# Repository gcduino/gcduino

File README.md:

GCDuino 
=======
© 2013-2014 Steve Dalton & Rod Christian

GCDuindo is a small low cost Arduino platform created by [Rod Christian](http://github.com/Rod-Refactor) and [Steve Dalton](http://github.com/spidie) of [Gold Coast TechSpace](http://gctechspace.org)

How to checkout this code
-------------------------

    git clone git@github.com:gctechshop/gcduino.git

Project Guide & Documentation
-----------------------------

For a work in progress project guide that we are using for the [Gold Coast TechSpace Discovery Workshops](http://discovery.gctechspace.org), please visit our [wiki](http://github.com/gcduino/gcduino/wiki)

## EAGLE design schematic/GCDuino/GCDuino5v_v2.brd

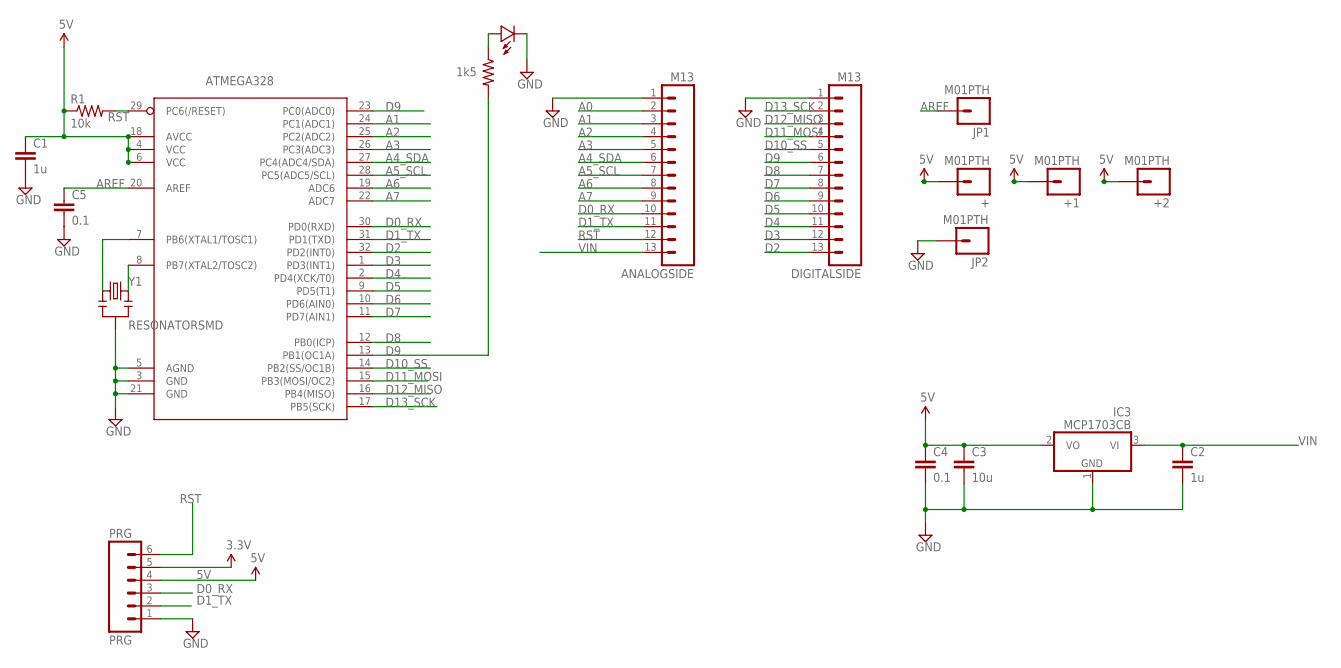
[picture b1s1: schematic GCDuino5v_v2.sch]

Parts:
+, +1, +2: M01PTH; 1X01
ANALOGSIDE: M13; 1X13
ATMEGA328: ATMega-328; TQFP32-08
C1, C2: 1u; 0805
C3: 10u; 0805-CAP
C4, C5: 0.1; 0805
DIGITALSIDE: M13; 1X13
IC3: MCP1703CB; SOT23
JP1, JP2: M01PTH; 1X01
PRG: PRG; 1X06
R1: 10k; 0805
R2: 1k5; 0805
U$2: LED0805; 0805-LED
Y1: RESONATORSMD; RESONATOR-SMD

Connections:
3.3V: PRG.5
5V: +.1, +1.1, +2.1, ATMEGA328.4 (VCC), ATMEGA328.6 (VCC), ATMEGA328.18 (AVCC), C1.1, C3.1, C4.1, IC3.2 (VO), PRG.4, R1.1
A0: ANALOGSIDE.2, ATMEGA328.23 (PC0(ADC0))
A1: ANALOGSIDE.3, ATMEGA328.24 (PC1(ADC1))
A2: ANALOGSIDE.4, ATMEGA328.25 (PC2(ADC2))
A3: ANALOGSIDE.5, ATMEGA328.26 (PC3(ADC3))
A4_SDA: ANALOGSIDE.6, ATMEGA328.27 (PC4(ADC4/SDA))
A5_SCL: ANALOGSIDE.7, ATMEGA328.28 (PC5(ADC5/SCL))
A6: ANALOGSIDE.8, ATMEGA328.19 (ADC6)
A7: ANALOGSIDE.9, ATMEGA328.22 (ADC7)
AREF: ATMEGA328.20 (AREF), C5.1, JP1.1
D0_RX: ANALOGSIDE.10, ATMEGA328.30 (PD0(RXD)), PRG.3
D1_TX: ANALOGSIDE.11, ATMEGA328.31 (PD1(TXD)), PRG.2
D2: ATMEGA328.32 (PD2(INT0)), DIGITALSIDE.13
D3: ATMEGA328.1 (PD3(INT1)), DIGITALSIDE.12
D4: ATMEGA328.2 (PD4(XCK/T0)), DIGITALSIDE.11
D5: ATMEGA328.9 (PD5(T1)), DIGITALSIDE.10
D6: ATMEGA328.10 (PD6(AIN0)), DIGITALSIDE.9
D7: ATMEGA328.11 (PD7(AIN1)), DIGITALSIDE.8
D8: ATMEGA328.12 (PB0(ICP)), DIGITALSIDE.7
D9: ATMEGA328.13 (PB1(OC1A)), DIGITALSIDE.6, R2.2
D10_SS: ATMEGA328.14 (PB2(SS/OC1B)), DIGITALSIDE.5
D11_MOSI: ATMEGA328.15 (PB3(MOSI/OC2)), DIGITALSIDE.4
D12_MISO: ATMEGA328.16 (PB4(MISO)), DIGITALSIDE.3
D13_SCK: ATMEGA328.17 (PB5(SCK)), DIGITALSIDE.2
GND: ANALOGSIDE.1, ATMEGA328.3 (GND), ATMEGA328.5 (AGND), ATMEGA328.21 (GND), C1.2, C2.2, C3.2, C4.2, C5.2, DIGITALSIDE.1, IC3.1 (GND), JP2.1, PRG.1, U$2.MINUS, Y1.2
unnamed: ATMEGA328.7 (PB6(XTAL1/TOSC1)), Y1.1
unnamed: R2.1, U$2.PLUS
unnamed: ATMEGA328.8 (PB7(XTAL2/TOSC2)), Y1.3
RST: ANALOGSIDE.12, ATMEGA328.29 (PC6(/RESET)), PRG.6, R1.2
VIN: ANALOGSIDE.13, C2.1, IC3.3 (VI)

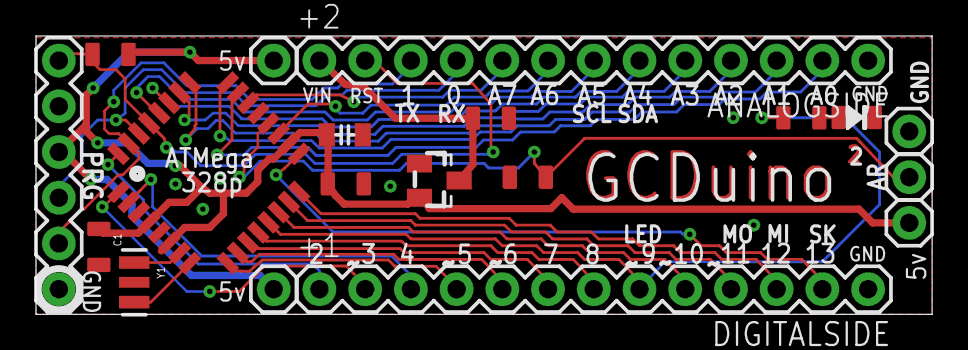
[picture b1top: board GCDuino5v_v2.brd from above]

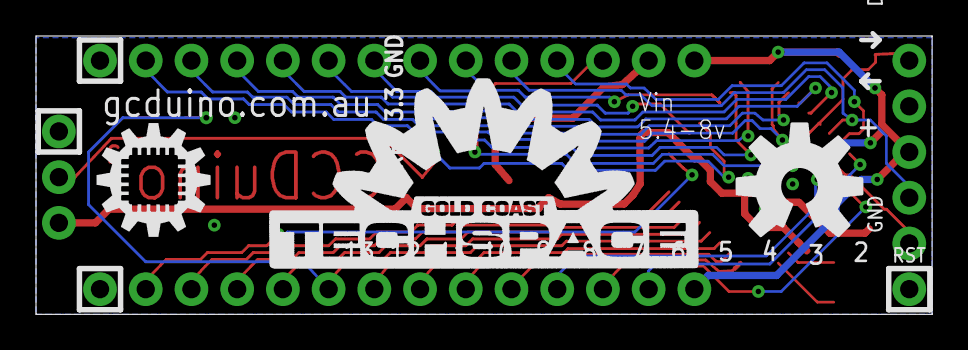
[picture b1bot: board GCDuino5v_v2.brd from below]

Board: 2 copper layers, 49.8 x 15.5 mm, 22 parts (3 on the bottom side), 30 nets.

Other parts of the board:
U$6: ID_LOGO_X0.25
U$7: OSHW-LOGO-L
U$9: GCTS_X0.5_TSILK

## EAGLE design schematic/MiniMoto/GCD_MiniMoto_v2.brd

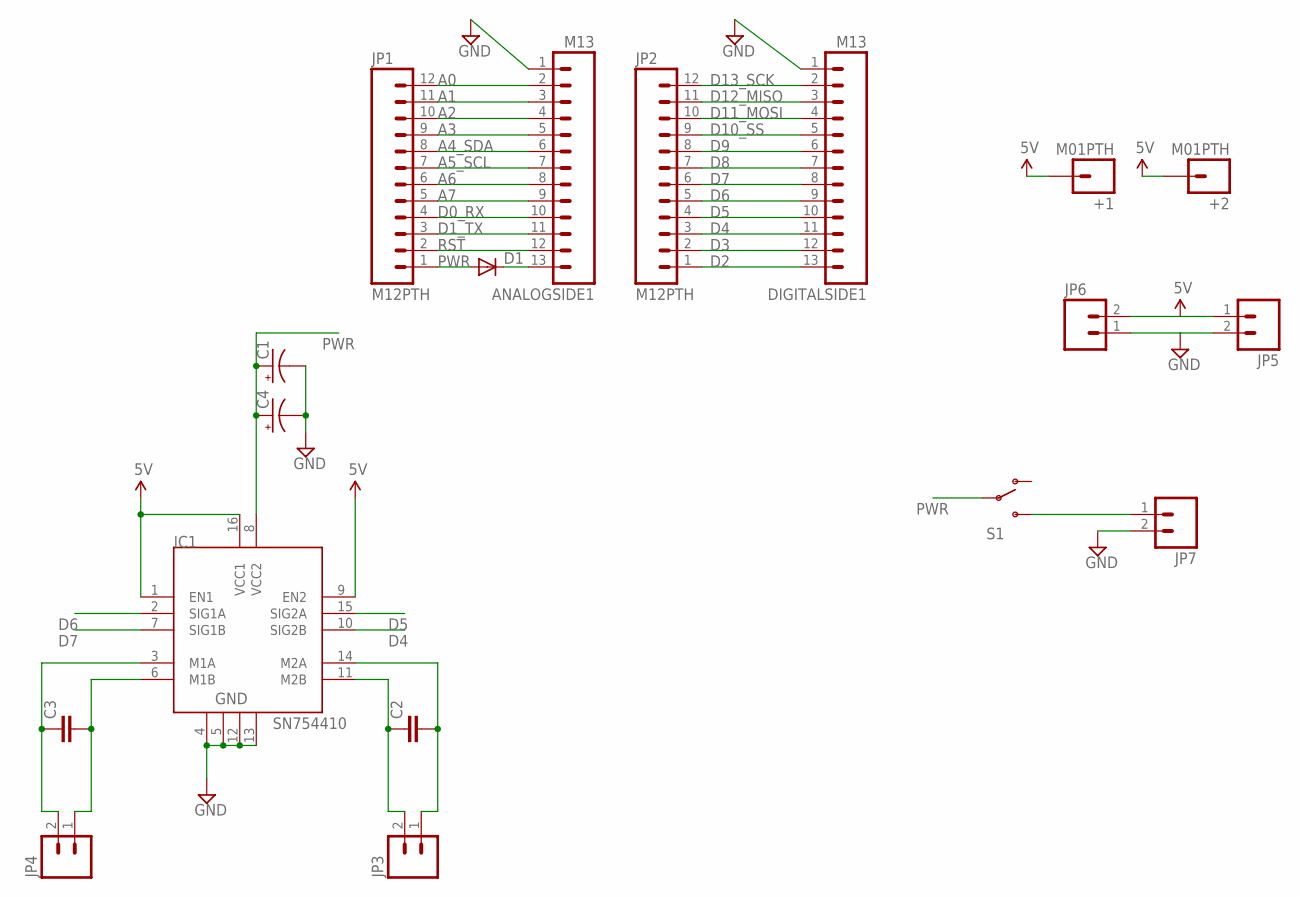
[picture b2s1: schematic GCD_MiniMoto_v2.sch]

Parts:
+1, +2: M01PTH; 1X01
ANALOGSIDE1: M13; 1X13
C1, C4: CAP_POLPTH1; CPOL-RADIAL-100UF-25V
C2, C3: CAPPTH1; CAP-PTH-5MM
D1: DIODESOD; SOD-323
DIGITALSIDE1: M13; 1X13
IC1: SN754410; DIP16
JP1, JP2: M12PTH; 1X12
JP3, JP4: M025MM; SCREWTERMINAL-5MM-2
JP5, JP6, JP7: M02PTH; 1X02
S1: SWITCH-SPDTPTH; SWITCH-SPDT

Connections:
5V: +1.1, +2.1, IC1.1 (EN1), IC1.9 (EN2), IC1.16 (VCC1), JP5.1, JP6.2
A0: ANALOGSIDE1.2, JP1.12
A1: ANALOGSIDE1.3, JP1.11
A2: ANALOGSIDE1.4, JP1.10
A3: ANALOGSIDE1.5, JP1.9
A4_SDA: ANALOGSIDE1.6, JP1.8
A5_SCL: ANALOGSIDE1.7, JP1.7
A6: ANALOGSIDE1.8, JP1.6
A7: ANALOGSIDE1.9, JP1.5
D0_RX: ANALOGSIDE1.10, JP1.4
D1_TX: ANALOGSIDE1.11, JP1.3
D2: DIGITALSIDE1.13, JP2.1
D3: DIGITALSIDE1.12, JP2.2
D4: DIGITALSIDE1.11, IC1.10 (SIG2B), JP2.3
D5: DIGITALSIDE1.10, IC1.15 (SIG2A), JP2.4
D6: DIGITALSIDE1.9, IC1.2 (SIG1A), JP2.5
D7: DIGITALSIDE1.8, IC1.7 (SIG1B), JP2.6
D8: DIGITALSIDE1.7, JP2.7
D9: DIGITALSIDE1.6, JP2.8
D10_SS: DIGITALSIDE1.5, JP2.9
D11_MOSI: DIGITALSIDE1.4, JP2.10
D12_MISO: DIGITALSIDE1.3, JP2.11
D13_SCK: DIGITALSIDE1.2, JP2.12
GND: ANALOGSIDE1.1, C1.2 (-), C4.2 (-), DIGITALSIDE1.1, IC1.4, IC1.5, IC1.12, IC1.13, JP5.2, JP6.1, JP7.2
unnamed: C3.1, IC1.3 (M1A), JP4.2
unnamed: C3.2, IC1.6 (M1B), JP4.1
unnamed: JP7.1, S1.3 (S)
unnamed: C2.1, IC1.11 (M2B), JP3.2
unnamed: C2.2, IC1.14 (M2A), JP3.1
unnamed: ANALOGSIDE1.13, D1.1 (C)
PWR: C1.1 (+), C4.1 (+), D1.2 (A), IC1.8 (VCC2), JP1.1, S1.2
RST: ANALOGSIDE1.12, JP1.2

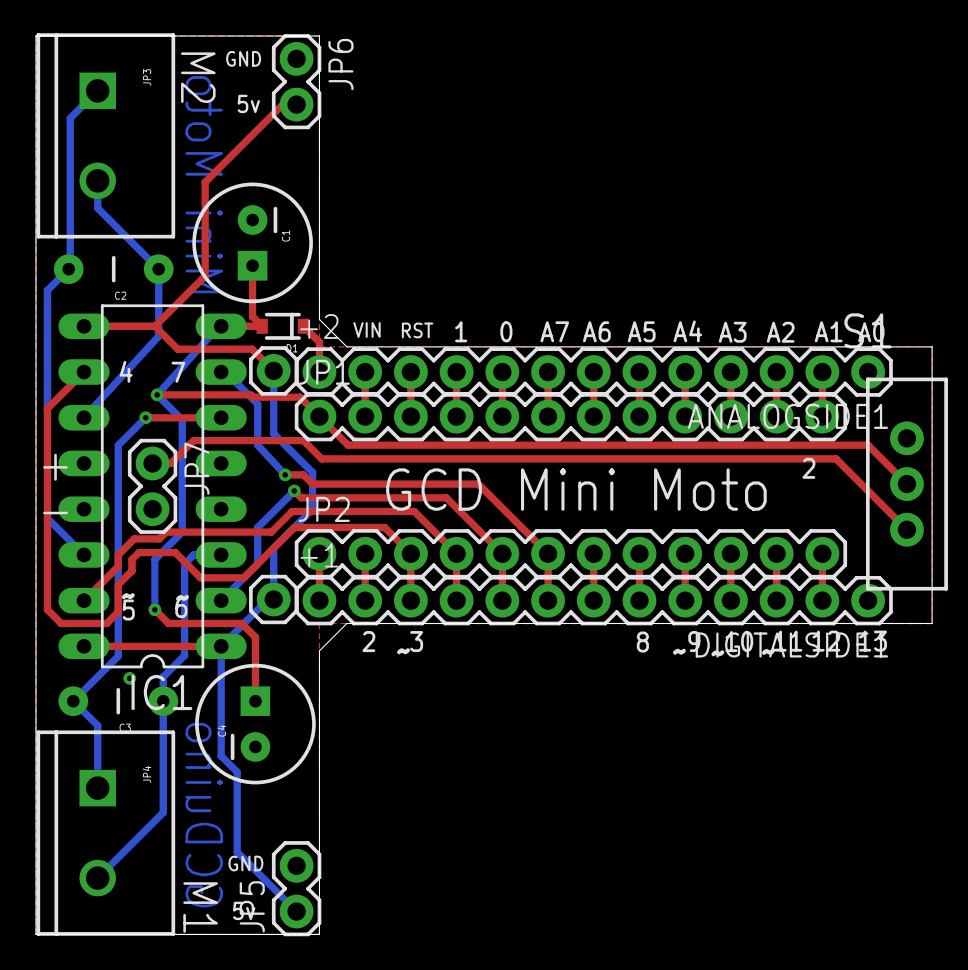
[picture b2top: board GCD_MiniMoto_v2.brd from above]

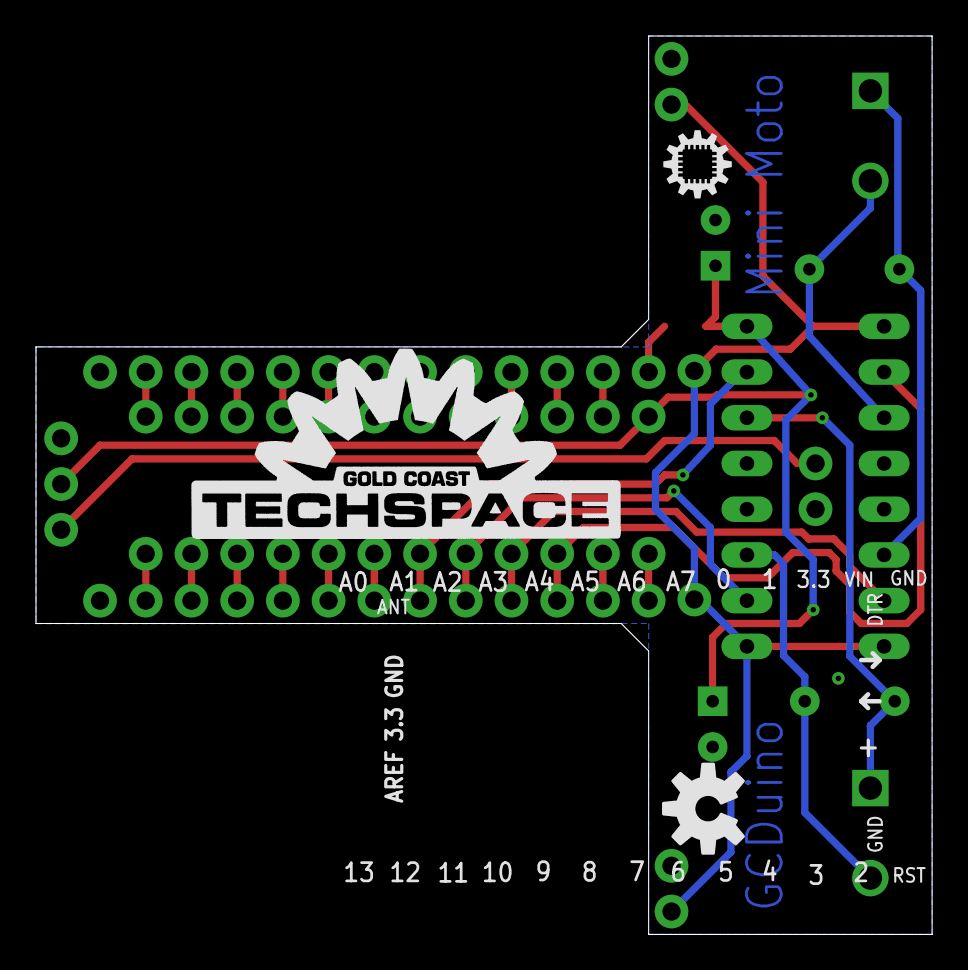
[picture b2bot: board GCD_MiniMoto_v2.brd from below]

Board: 2 copper layers, 49.8 x 49.9 mm, 21 parts (3 on the bottom side), 32 nets.

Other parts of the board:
U$5: GCTS_X0.5_TSILK
U$6: ID_LOGO_X0.15
U$7: OSHW-LOGO-M

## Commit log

2013-11-07 initial
2013-11-07 readme
2013-11-23 minimoto
2013-12-18 simpler minimoto
2013-12-26 images and code
2013-12-26 links to wiki
2013-12-26 extension material
2013-12-26 fixed screenshot length
2013-12-26 fixed screenshot to have compiled message
2013-12-29 Summer example
2013-12-29 added RTC
2014-01-02 added bump sensor example
2014-01-02 reorg
2014-01-02 working with LCD now
2014-01-05 modularized and added unit tests
2014-01-05 Refactored so we can use a makefile
2014-01-05 changed ino so that it will work with IDE and makefile
2014-01-07 toastmasters
2014-01-07 added fritzing and skips code
2014-01-07 redid screenshots
2014-01-13 set pin high before adding interupt
2014-01-22 added melody
2014-01-28 changed to a library
2014-03-13 added initialize
2014-03-21 Added schematics
2014-05-12 Added PrjectGuide V2, pinout diagram and Fritzing Part
2014-05-18 fixed link to wiki
2014-05-18 extra images'

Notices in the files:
parts and their libraries:
SparkFun-Connectors: Licensing: CC v3.0 Share-Alike You are welcome to use this library for commercial purposes.
